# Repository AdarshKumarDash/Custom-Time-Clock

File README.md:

# Custom-Time-Clock
This is a custom digital clock that I made with my own built PCB, prototyping and programming

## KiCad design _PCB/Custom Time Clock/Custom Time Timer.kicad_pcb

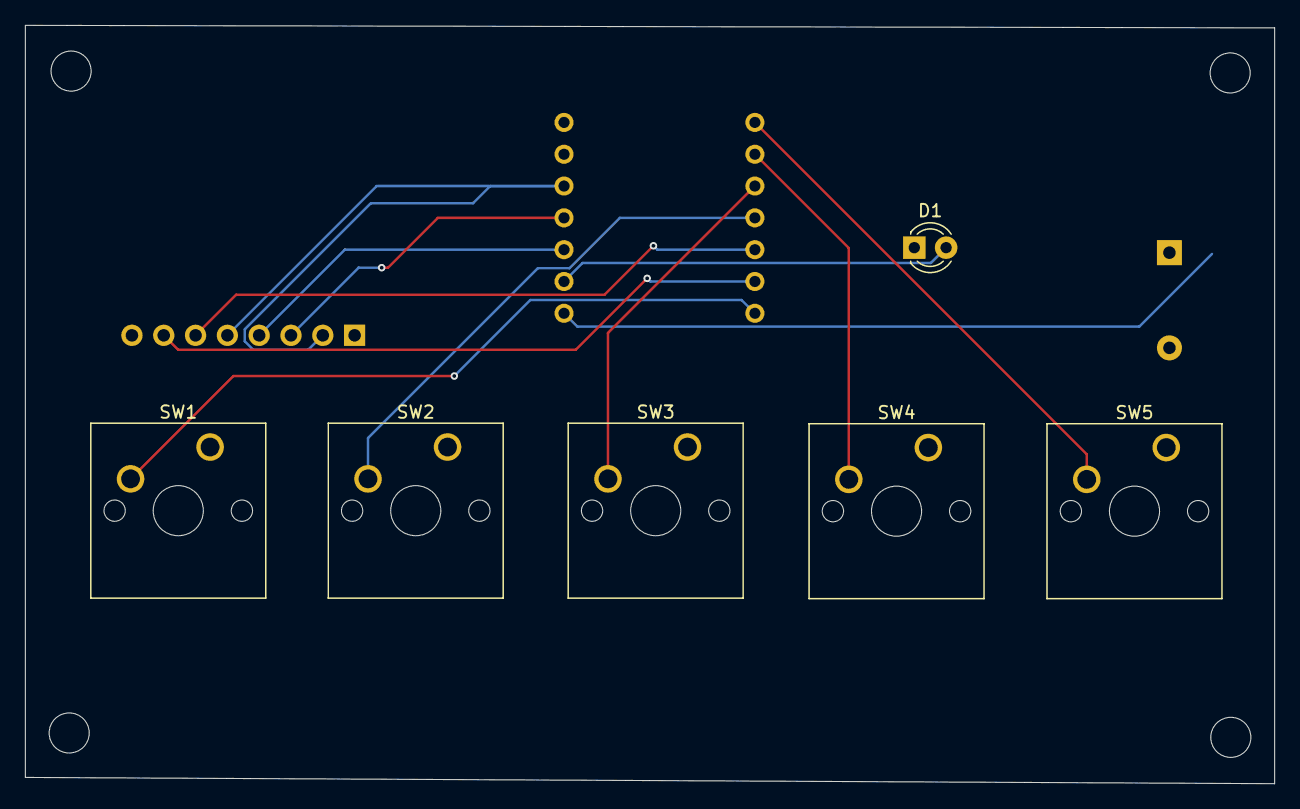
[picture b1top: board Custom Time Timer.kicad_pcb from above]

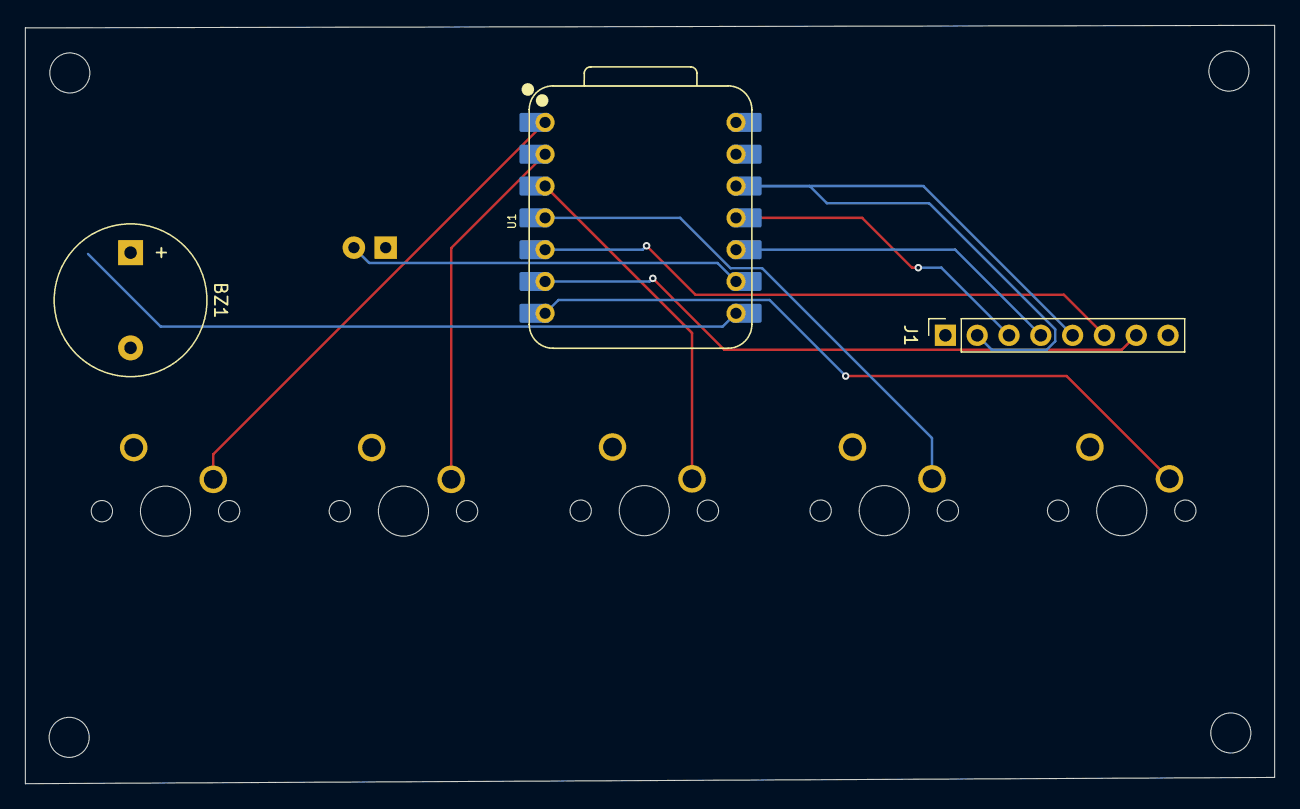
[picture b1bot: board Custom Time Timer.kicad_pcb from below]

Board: 2 copper layers, 99.8 x 60.6 mm, 13 parts (3 on the bottom side), 13 nets.

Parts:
BZ1: Buzzer; Buzzer_12x9.5RM7.6
D1: LED; LED_D3.0mm
H1, H2, H3, H4: MountingHole; MountingHole_3.2mm_M3
J1: Conn_01x08_Pin; PinSocket_1x08_P2.54mm_Vertical
SW1, SW2, SW3, SW4, SW5: SW_Push; SW_Cherry_MX_1.00u_PCB
U1: XIAO-ESP32-C3-SMD; XIAO-ESP32-C3-DIP

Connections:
+3.3V: J1.2, J1.5, U1.12 (3V3_OUT)
/CS: J1.7, U1.6 (D5)
/DC: J1.6, U1.5 (D4)
/SCL: J1.4, U1.10 (D9/BOOT)
/SDA: J1.3, U1.11 (D10)
GND: BZ1.2 (-), D1.1 (K), J1.1, J1.8, SW1.1, SW2.1, SW3.1, SW4.1, SW5.1, U1.13 (GND)
unnamed: BZ1.1 (+), U1.8 (D7)
unnamed: D1.2 (A), U1.9 (D8)
unnamed: SW5.2, U1.1 (D0)
unnamed: SW4.2, U1.2 (D1)
unnamed: SW3.2, U1.3 (D2)
unnamed: SW2.2, U1.4 (D3)
unnamed: SW1.2, U1.7 (D6)
